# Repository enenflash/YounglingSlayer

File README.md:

# YounglingSlayer
Team repository for Robocup Junior Lightweight Australia 2024

## Team Info
- Members: Isabelle Tang (Captain), Ryan Beikrasouli (Programmer), Cruz Barry-Hardy (3D Designer), Albie Gardiner (3D Designer)
- State: Western Australia
- School: Rossmoyne Senior High School

## Programming
We use C++ in [ArduinoIDE](https://www.arduino.cc/en/software/) to program our microcontroller (Teensy 4.1). (See code-explanations)
We also use Raspberry Pi Pico as part of our line sensor.

## 3D Printing
We design our parts in [Fusion360](https://www.autodesk.com/au/products/fusion-360/education). (See mechanical design/)
All parts are printed in PLA.

## PCB Design
We design our PCBs in [KiCAD 7.0](https://www.kicad.org/) and order from [JLCPCB](https://jlcpcb.com/). (See pcbs/).
The schematics are based on circuits we tested using breadboards.

All designs are original other than the [BBR IR Seeker](https://irseeker.buildingblockrobotics.com/)

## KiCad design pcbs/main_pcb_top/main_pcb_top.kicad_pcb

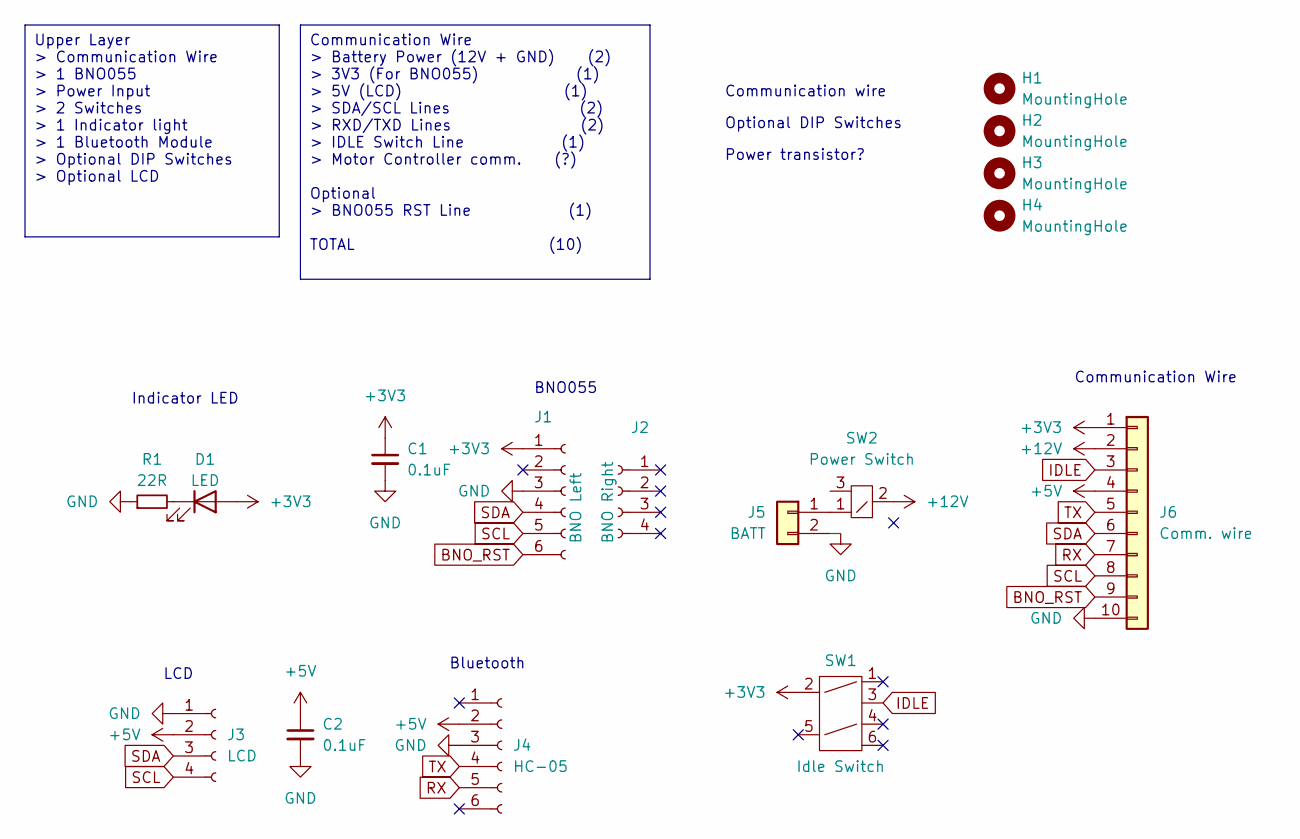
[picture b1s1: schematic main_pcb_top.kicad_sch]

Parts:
C1, C2: 0.1uF; C_0402_1005Metric
D1: LED; LED_0805_2012Metric
H1, H2, H3, H4: MountingHole; MountingHole_3.2mm_M3_Pad
J1: BNO Left; PinSocket_1x06_P2.54mm_Vertical
J2: BNO Right; PinSocket_1x04_P2.54mm_Vertical
J3: LCD; PinSocket_1x04_P2.54mm_Vertical
J4: HC-05; PinSocket_1x06_P2.54mm_Vertical
J5: BATT; JST_XH_B2B-XH-A_1x02_P2.50mm_Vertical
J6: Comm. wire; IDC-Header_2x05_P2.54mm_Vertical
R1: 22R; R_0805_2012Metric
SW1: Idle Switch; Switch_DPDT_S2060
SW2: Power Switch; Switch_SPDT_S2070

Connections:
+3V3: C1.1, D1.2 (A), J1.1, J6.1, SW1.2
+5V: C2.1, J3.2, J4.2, J6.4
+12V: J6.2, SW2.2
BNO_RST: J1.6, J6.9
GND: C1.2, C2.2, J1.3, J3.1, J4.3, J5.2, J6.10, R1.1
IDLE: J6.3, SW1.3
unnamed: D1.1 (K), R1.2
unnamed: J5.1, SW2.1
RX: J4.5, J6.7
SCL: J1.5, J3.4, J6.8
SDA: J1.4, J3.3, J6.6
TX: J4.4, J6.5

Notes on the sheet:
Upper Layer > Communication Wire > 1 BNO055 > Power Input > 2 Switches > 1 Indicator light > 1 Bluetooth Module > Optional DIP Switches > Optional LCD
Communication Wire > Battery Power (12V + GND) (2) > 3V3 (For BNO055) (1) > 5V (LCD) (1) > SDA/SCL Lines (2) > RXD/TXD Lines (2) > IDLE Switch Line (1) > Motor Controller comm. (?) Optional > BNO055 RST Line (1) TOTAL (10)
Power transistor?
Bluetooth
Communication wire
Optional DIP Switches
BNO055
LCD
Indicator LED
Communication Wire

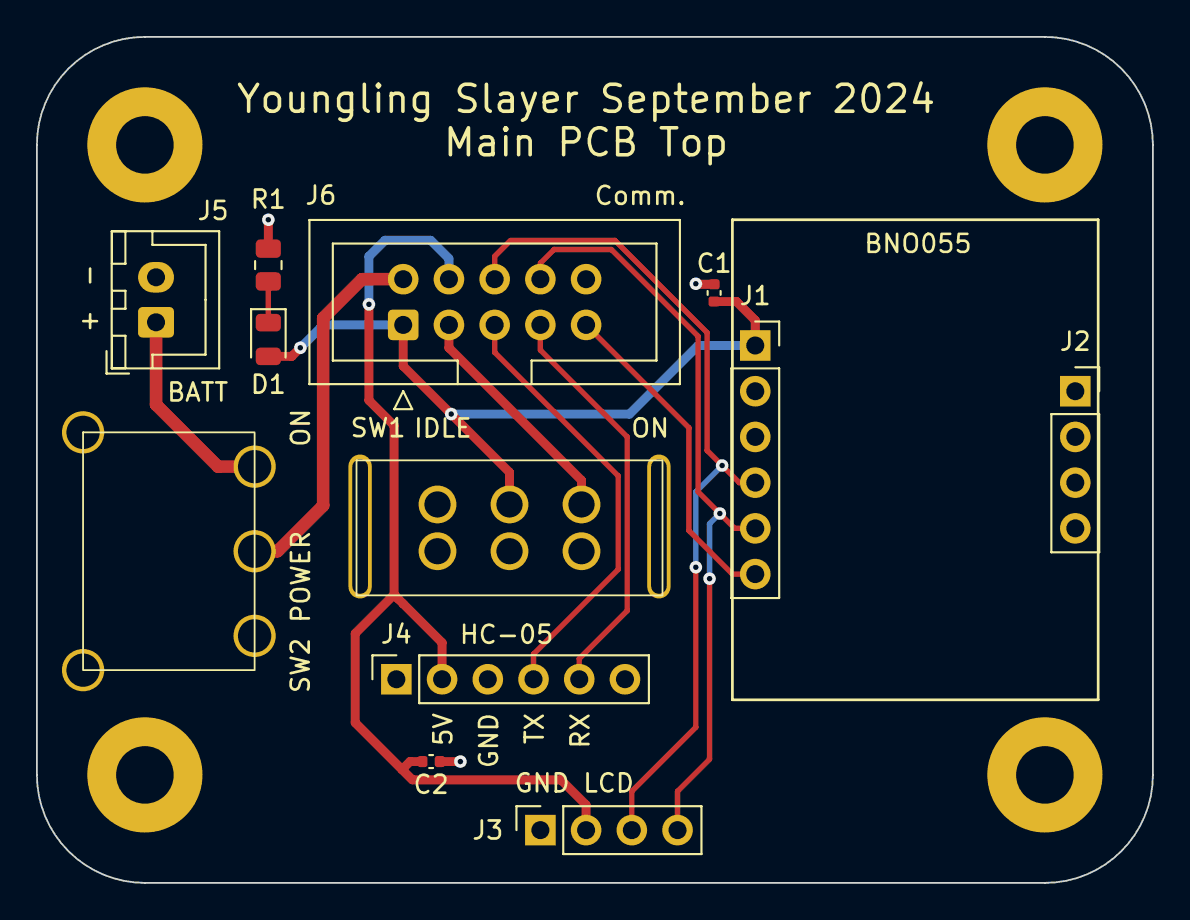
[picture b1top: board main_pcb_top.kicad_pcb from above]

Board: 2 copper layers, 62.0 x 47.0 mm, 16 parts (0 on the bottom side), 12 nets.

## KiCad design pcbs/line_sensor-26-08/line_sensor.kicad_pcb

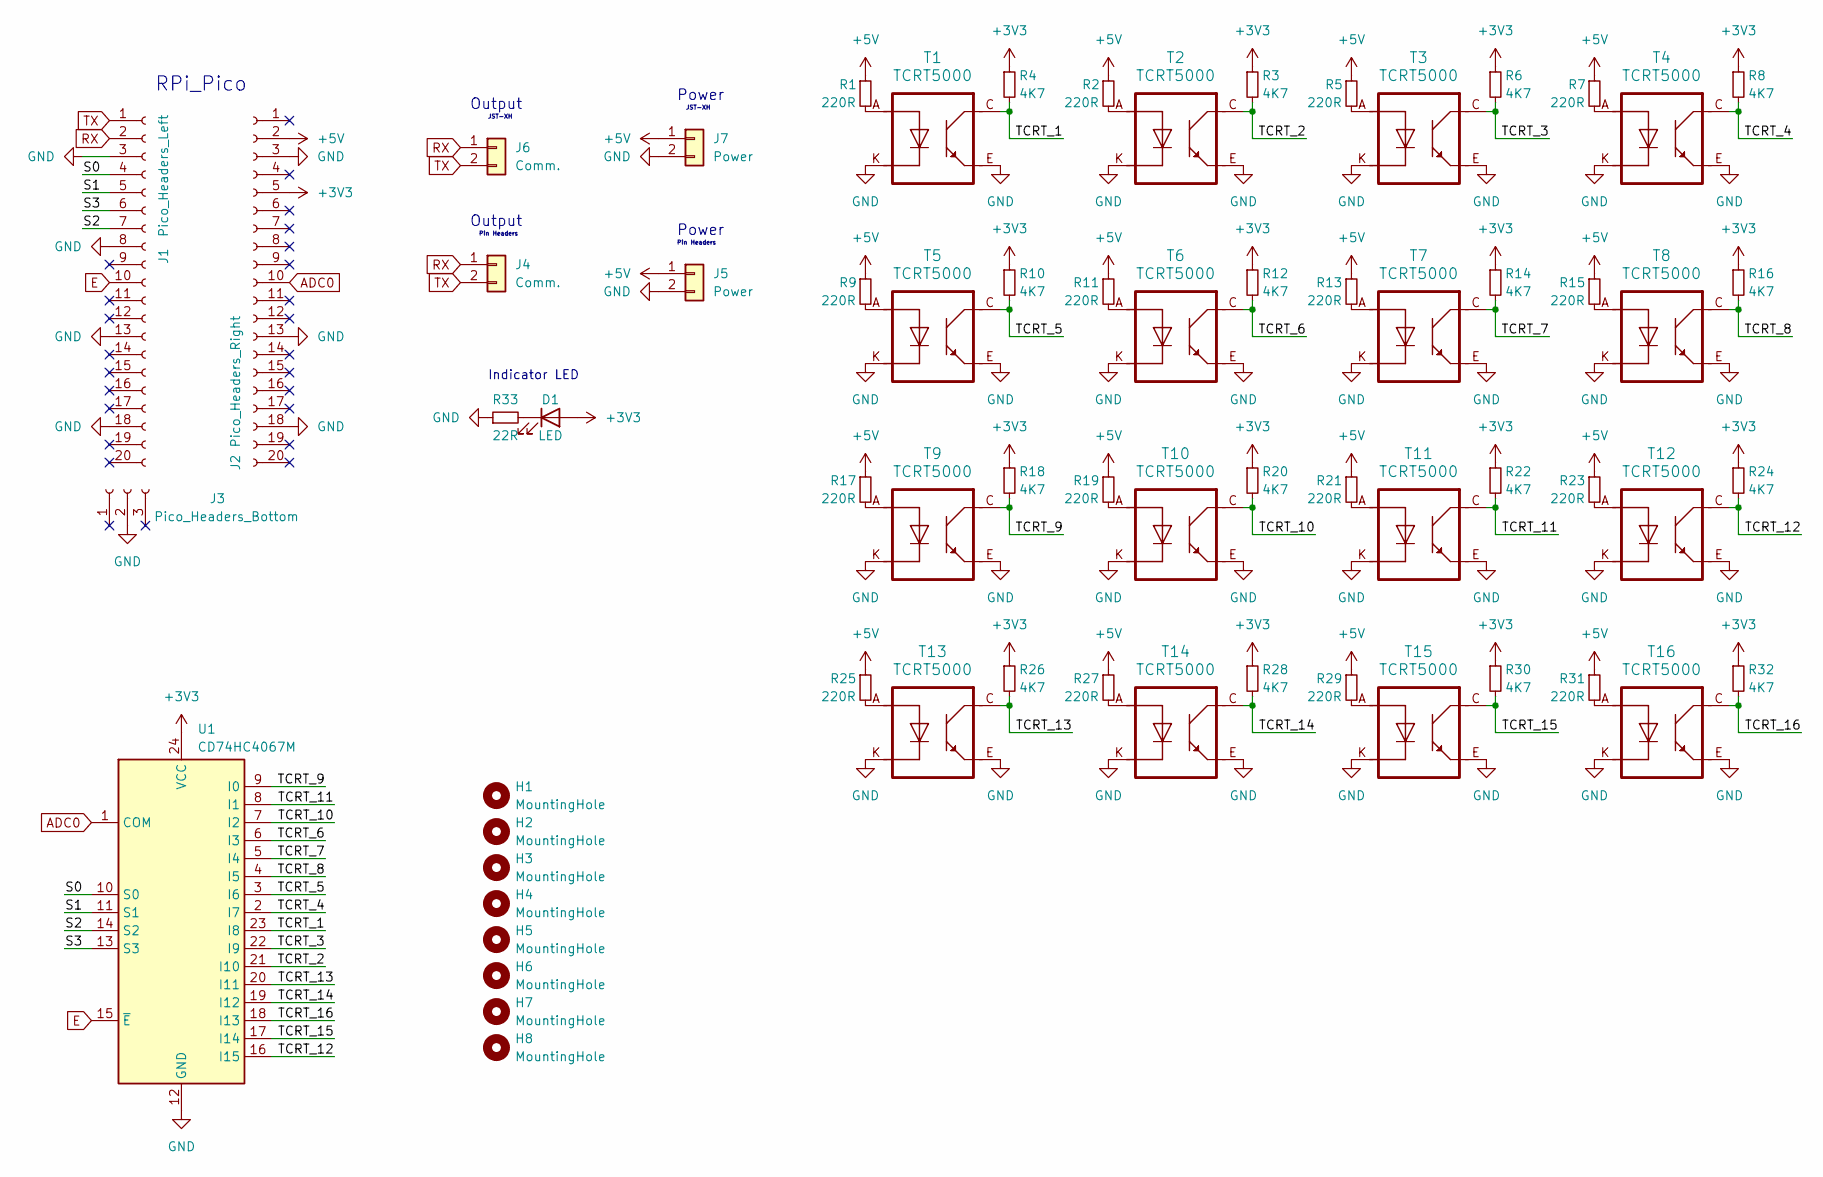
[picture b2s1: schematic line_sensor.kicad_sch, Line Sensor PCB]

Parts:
D1: LED; LED_0805_2012Metric
H1, H2, H3, H4, H5, H6, H7, H8: MountingHole; MountingHole_3.2mm_M3_Pad
J1: Pico_Headers_Left; PinSocket_1x20_P2.54mm_Vertical
J2: Pico_Headers_Right; PinSocket_1x20_P2.54mm_Vertical
J3: Pico_Headers_Bottom; PinSocket_1x03_P2.54mm_Vertical
J4: Comm.; PinSocket_1x02_P2.54mm_Vertical
J5: Power; PinSocket_1x02_P2.54mm_Vertical
J6: Comm.; JST_XH_B2B-XH-AM_1x02_P2.50mm_Vertical
J7: Power; JST_XH_B2B-XH-AM_1x02_P2.50mm_Vertical
R1, R2, R5, R7, R9, R11, R13, R15, R17, R19, R21, R23, R25, R27, R29, R31: 220R; R_0805_2012Metric
R3, R4, R6, R8, R10, R12, R14, R16, R18, R20, R22, R24, R26, R28, R30, R32: 4K7; R_0805_2012Metric
R33: 22R; R_0805_2012Metric
T1, T2, T3, T4, T5, T6, T7, T8, T9, T10, T11, T12, T13, T14, T15, T16: TCRT5000
U1: CD74HC4067M; SOIC-24W_7.5x15.4mm_P1.27mm

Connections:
+3V3: D1.2 (A), J2.5, R3.1, R4.1, R6.1, R8.1, R10.1, R12.1, R14.1, R16.1, R18.1, R20.1, R22.1, R24.1, R26.1, R28.1, R30.1, R32.1, U1.24 (VCC)
+5V: J2.2, J5.1, J7.1, R1.1, R2.1, R5.1, R7.1, R9.1, R11.1, R13.1, R15.1, R17.1, R19.1, R21.1, R23.1, R25.1, R27.1, R29.1, R31.1
/S0: J1.4, U1.10 (S0)
/S1: J1.5, U1.11 (S1)
/S2: J1.7, U1.14 (S2)
/S3: J1.6, U1.13 (S3)
/TCRT_1: R4.2, T1.C (Collector), U1.23 (I8)
/TCRT_2: R3.2, T2.C (Collector), U1.21 (I10)
/TCRT_3: R6.2, T3.C (Collector), U1.22 (I9)
/TCRT_4: R8.2, T4.C (Collector), U1.2 (I7)
/TCRT_5: R10.2, T5.C (Collector), U1.3 (I6)
/TCRT_6: R12.2, T6.C (Collector), U1.6 (I3)
/TCRT_7: R14.2, T7.C (Collector), U1.5 (I4)
/TCRT_8: R16.2, T8.C (Collector), U1.4 (I5)
/TCRT_9: R18.2, T9.C (Collector), U1.9 (I0)
/TCRT_10: R20.2, T10.C (Collector), U1.7 (I2)
/TCRT_11: R22.2, T11.C (Collector), U1.8 (I1)
/TCRT_12: R24.2, T12.C (Collector), U1.16 (I15)
/TCRT_13: R26.2, T13.C (Collector), U1.20 (I11)
/TCRT_14: R28.2, T14.C (Collector), U1.19 (I12)
/TCRT_15: R30.2, T15.C (Collector), U1.17 (I14)
/TCRT_16: R32.2, T16.C (Collector), U1.18 (I13)
ADC0: J2.10, U1.1 (COM)
E: J1.10, U1.15 (~E)
GND: J1.3, J1.8, J1.13, J1.18, J2.3, J2.13, J2.18, J3.2, J5.2, J7.2, R33.1, T1.E (Emitter), T1.K (Cathode), T2.E (Emitter), T2.K (Cathode), T3.E (Emitter), T3.K (Cathode), T4.E (Emitter), T4.K (Cathode), T5.E (Emitter), T5.K (Cathode), T6.E (Emitter), T6.K (Cathode), T7.E (Emitter), T7.K (Cathode), T8.E (Emitter), T8.K (Cathode), T9.E (Emitter), T9.K (Cathode), T10.E (Emitter), T10.K (Cathode), T11.E (Emitter), T11.K (Cathode), T12.E (Emitter), T12.K (Cathode), T13.E (Emitter), T13.K (Cathode), T14.E (Emitter), T14.K (Cathode), T15.E (Emitter), T15.K (Cathode), T16.E (Emitter), T16.K (Cathode), U1.12 (GND)
unnamed: D1.1 (K), R33.2
unnamed: R1.2, T1.A (Anode)
unnamed: R2.2, T2.A (Anode)
unnamed: R5.2, T3.A (Anode)
unnamed: R7.2, T4.A (Anode)
unnamed: R9.2, T5.A (Anode)
unnamed: R11.2, T6.A (Anode)
unnamed: R13.2, T7.A (Anode)
unnamed: R15.2, T8.A (Anode)
unnamed: R17.2, T9.A (Anode)
unnamed: R19.2, T10.A (Anode)
unnamed: R21.2, T11.A (Anode)
unnamed: R23.2, T12.A (Anode)
unnamed: R25.2, T13.A (Anode)
unnamed: R27.2, T14.A (Anode)
unnamed: R29.2, T15.A (Anode)
unnamed: R31.2, T16.A (Anode)
RX: J1.2, J4.1, J6.1
TX: J1.1, J4.2, J6.2

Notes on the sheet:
Output
Power
RPi_Pico
JST-XH
Pin Headers
Indicator LED

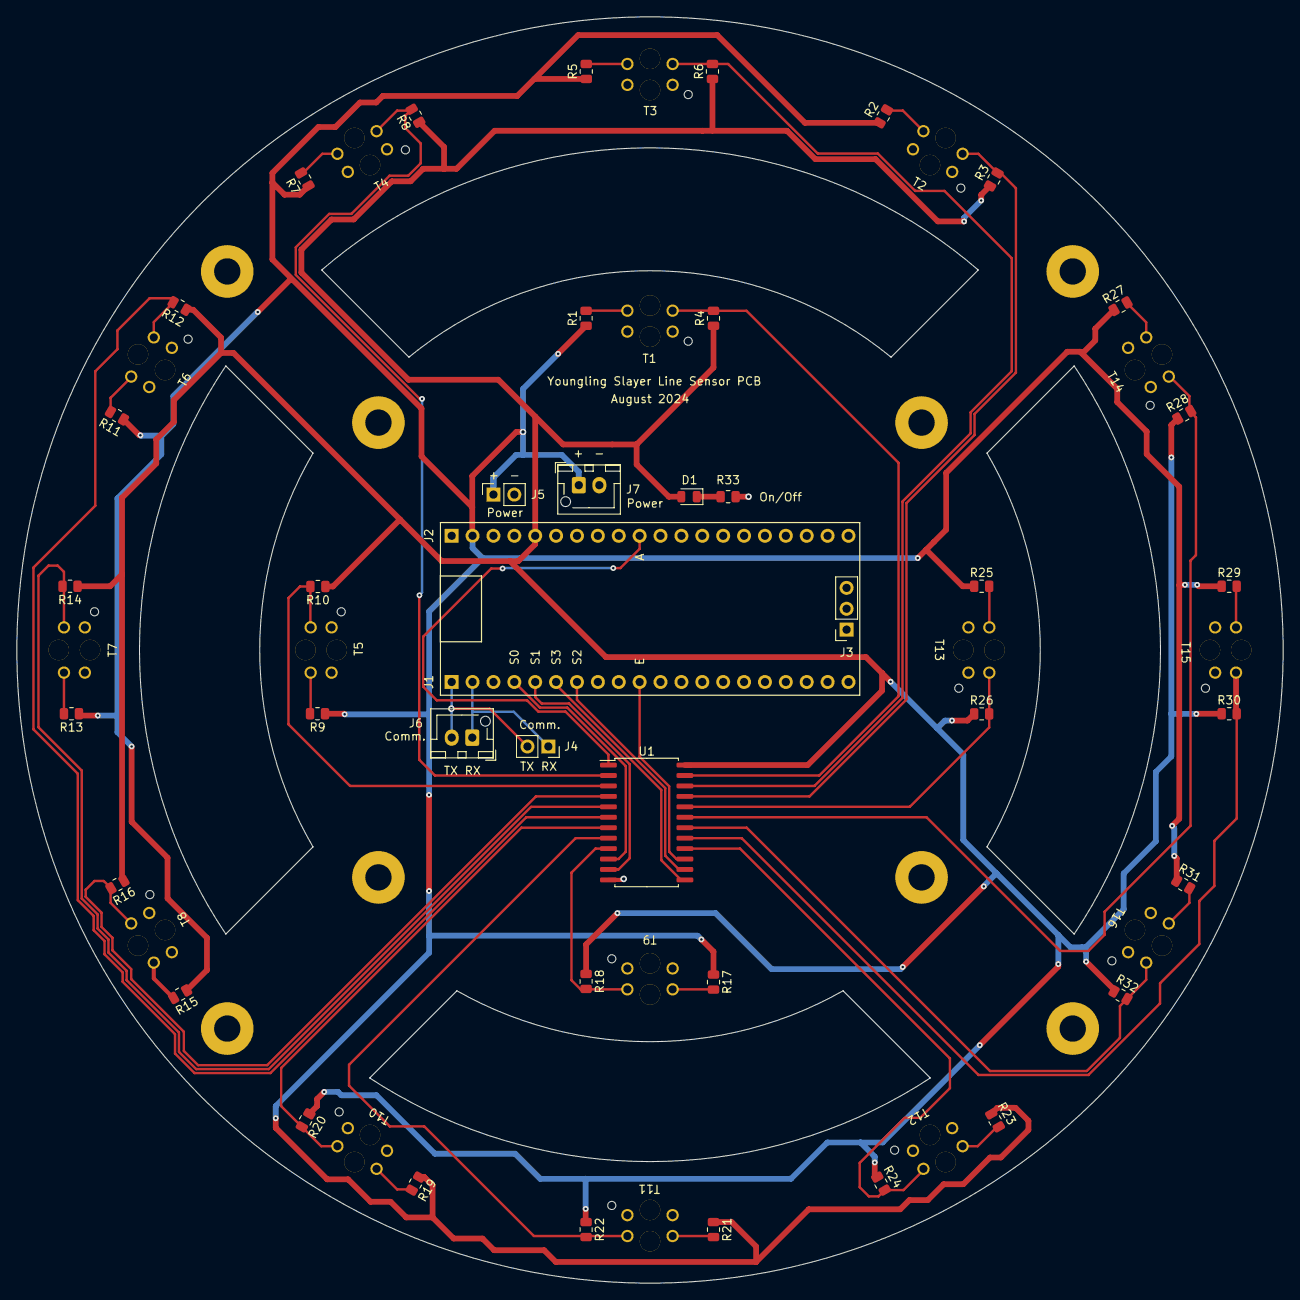
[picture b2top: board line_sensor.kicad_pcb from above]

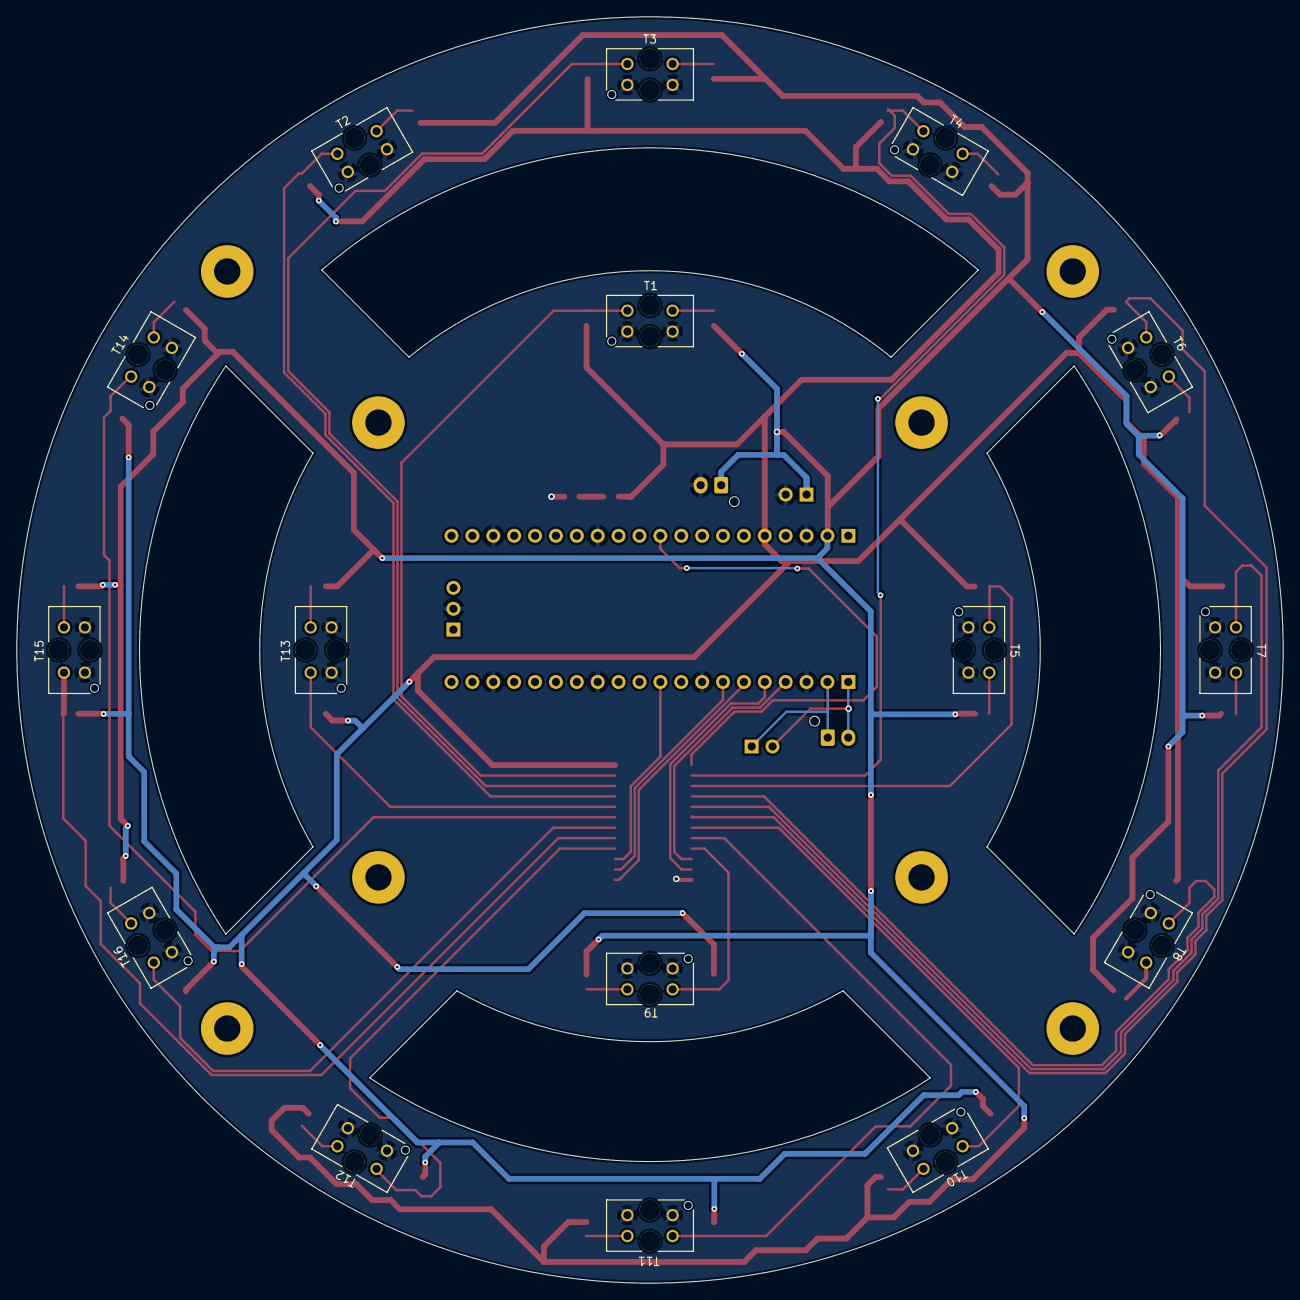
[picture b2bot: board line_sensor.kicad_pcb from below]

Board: 2 copper layers, 154.0 x 154.0 mm, 66 parts (16 on the bottom side), 44 nets.

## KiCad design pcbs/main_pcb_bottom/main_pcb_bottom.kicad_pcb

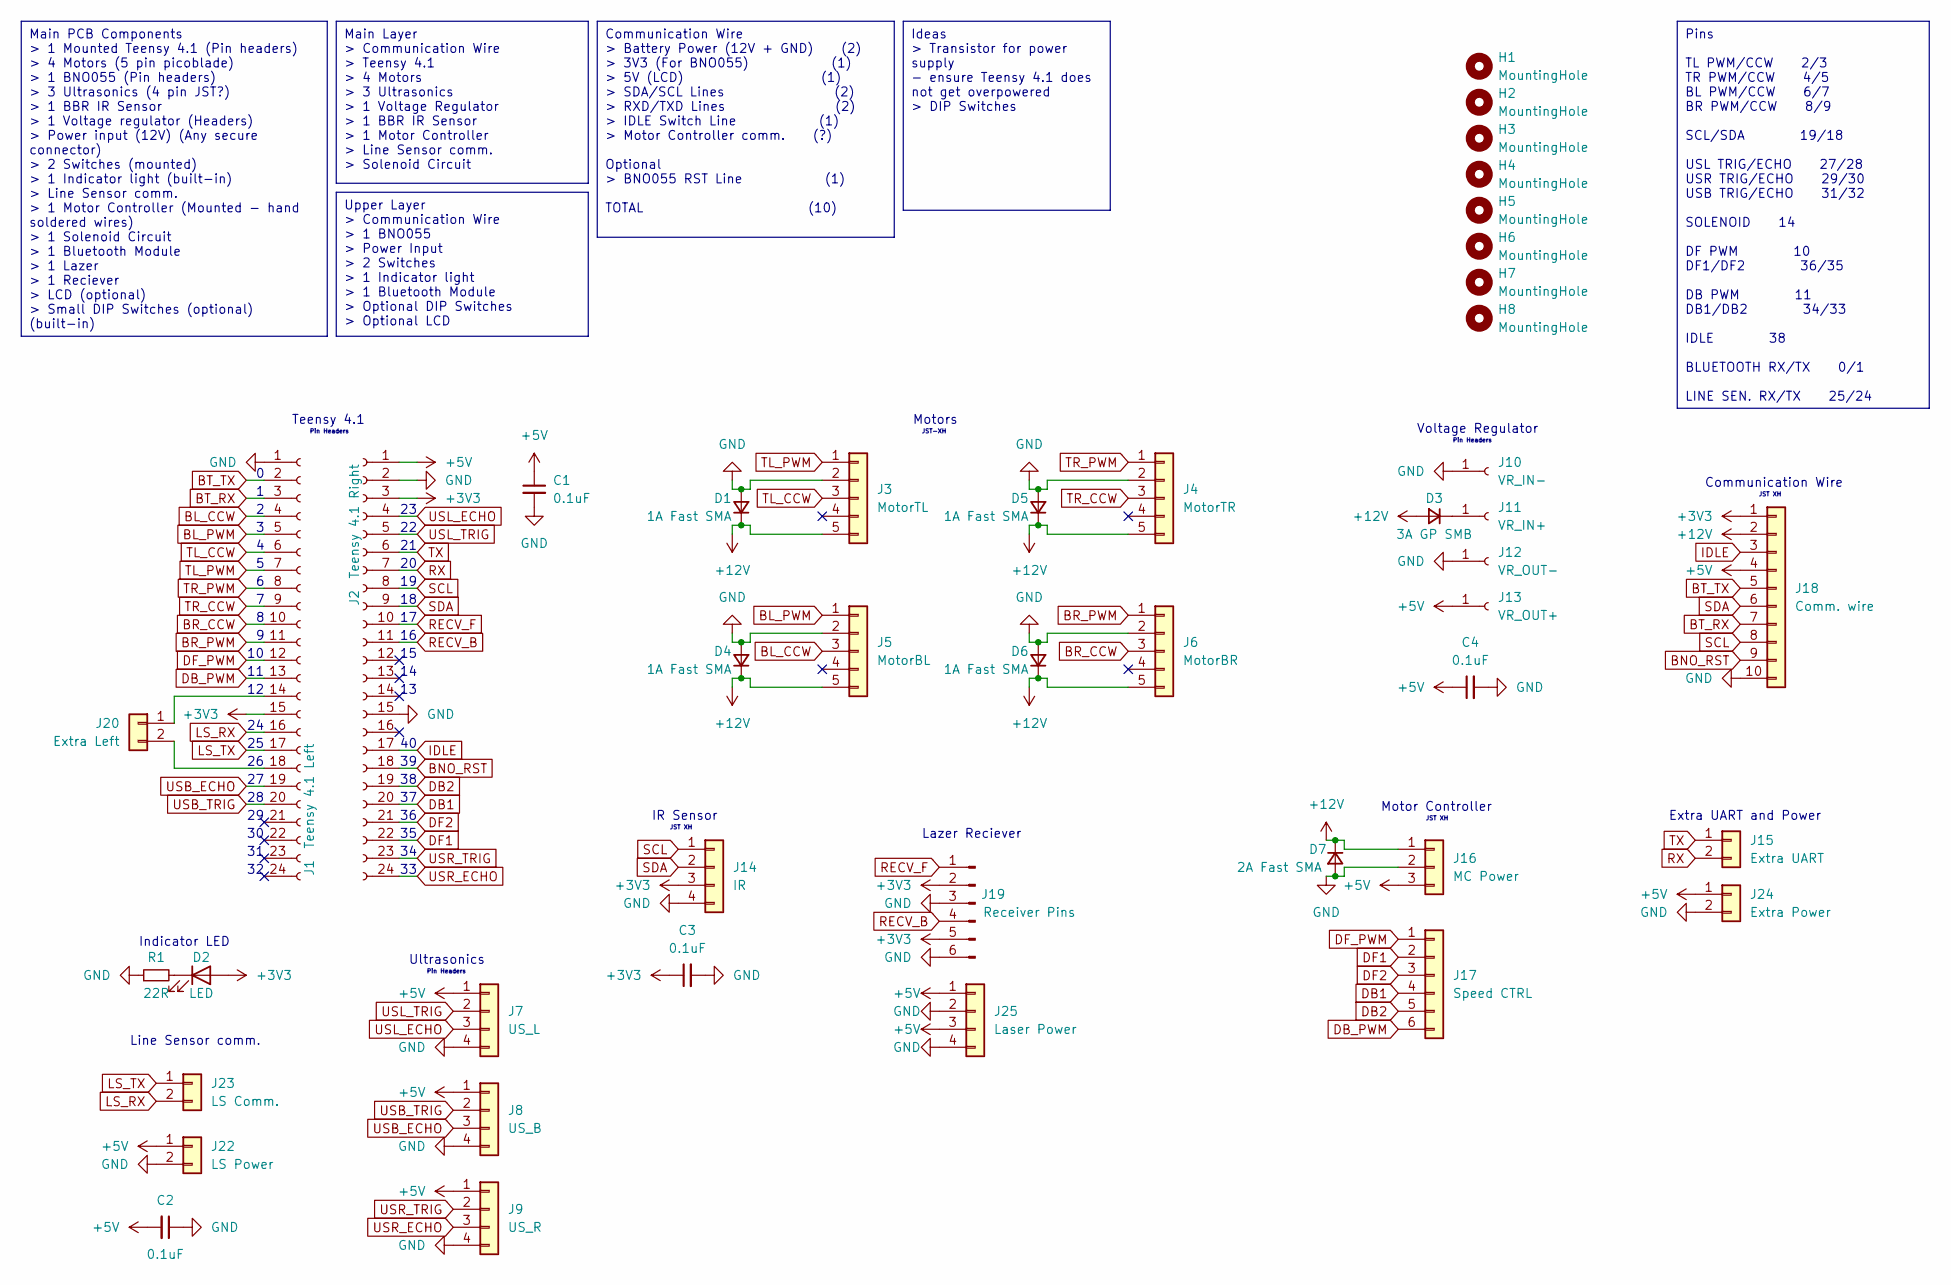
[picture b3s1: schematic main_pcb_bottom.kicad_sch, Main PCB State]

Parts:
C1, C2, C3, C4: 0.1uF; C_0402_1005Metric
D1, D4, D5, D6: 1A Fast SMA; D_SMA
D2: LED; LED_0805_2012Metric_Pad1.15x1.40mm_HandSolder
D3: 3A GP SMB; D_SMB
D7: 2A Fast SMA; D_SMA
H1, H2, H3, H4, H5, H6, H7, H8: MountingHole; MountingHole_3.2mm_M3_Pad
J1: Teensy 4.1 Left; PinSocket_1x24_P2.54mm_Vertical
J2: Teensy 4.1 Right; PinSocket_1x24_P2.54mm_Vertical
J3: MotorTL; JST_XH_B5B-XH-AM_1x05_P2.50mm_Vertical
J4: MotorTR; JST_XH_B5B-XH-AM_1x05_P2.50mm_Vertical
J5: MotorBL; JST_XH_B5B-XH-AM_1x05_P2.50mm_Vertical
J6: MotorBR; JST_XH_B5B-XH-AM_1x05_P2.50mm_Vertical
J7: US_L; JST_XH_B4B-XH-AM_1x04_P2.50mm_Vertical
J8: US_B; JST_XH_B4B-XH-AM_1x04_P2.50mm_Vertical
J9: US_R; JST_XH_B4B-XH-AM_1x04_P2.50mm_Vertical
J10: VR_IN-; PinSocket_1x01_P2.54mm_Vertical
J11: VR_IN+; PinSocket_1x01_P2.54mm_Vertical
J12: VR_OUT-; PinSocket_1x01_P2.54mm_Vertical
J13: VR_OUT+; PinSocket_1x01_P2.54mm_Vertical
J14: IR; JST_XH_B4B-XH-AM_1x04_P2.50mm_Vertical
J15: Extra UART; JST_XH_B2B-XH-AM_1x02_P2.50mm_Vertical
J16: MC Power; JST_XH_B3B-XH-AM_1x03_P2.50mm_Vertical
J17: Speed CTRL; JST_XH_B6B-XH-AM_1x06_P2.50mm_Vertical
J18: Comm. wire; IDC-Header_2x05_P2.54mm_Vertical
J19: Receiver Pins; PinHeader_1x06_P2.54mm_Vertical
J20: Extra Left; PinSocket_1x02_P2.54mm_Vertical
J22: LS Power; JST_XH_B2B-XH-AM_1x02_P2.50mm_Vertical
J23: LS Comm.; JST_XH_B2B-XH-AM_1x02_P2.50mm_Vertical
J24: Extra Power; JST_XH_B2B-XH-AM_1x02_P2.50mm_Vertical
J25: Laser Power; PinHeader_1x04_P2.54mm_Vertical
R1: 22R; R_0805_2012Metric_Pad1.20x1.40mm_HandSolder

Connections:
+3V3: C3.1, D2.2 (A), J1.15, J2.3, J14.3, J18.1, J19.2, J19.5
+5V: C1.1, C2.2, C4.1, J2.1, J7.1, J8.1, J9.1, J13.1, J16.3, J18.4, J22.1, J24.1, J25.1, J25.3
+12V: D1.1 (K), D3.2 (A), D4.1 (K), D5.1 (K), D6.1 (K), D7.1 (K), J3.5, J4.5, J5.5, J6.5, J16.1, J18.2
BL_CCW: J1.4, J5.3
BL_PWM: J1.5, J5.1
BNO_RST: J2.18, J18.9
BR_CCW: J1.10, J6.3
BR_PWM: J1.11, J6.1
BT_RX: J1.3, J18.7
BT_TX: J1.2, J18.5
DB1: J2.20, J17.4
DB2: J2.19, J17.5
DB_PWM: J1.13, J17.6
DF1: J2.22, J17.2
DF2: J2.21, J17.3
DF_PWM: J1.12, J17.1
GND: C1.2, C2.1, C3.2, C4.2, D1.2 (A), D4.2 (A), D5.2 (A), D6.2 (A), D7.2 (A), J1.1, J2.2, J2.15, J3.2, J4.2, J5.2, J6.2, J7.4, J8.4, J9.4, J10.1, J12.1, J14.4, J16.2, J18.10, J19.3, J19.6, J22.2, J24.2, J25.2, J25.4, R1.1
IDLE: J2.17, J18.3
LS_RX: J1.16, J23.2
LS_TX: J1.17, J23.1
unnamed: D2.1 (K), R1.2
unnamed: D3.1 (K), J11.1
unnamed: J1.14, J20.1
unnamed: J1.18, J20.2
RECV_B: J2.11, J19.4
RECV_F: J2.10, J19.1
RX: J2.7, J15.2
SCL: J2.8, J14.1, J18.8
SDA: J2.9, J14.2, J18.6
TL_CCW: J1.6, J3.3
TL_PWM: J1.7, J3.1
TR_CCW: J1.9, J4.3
TR_PWM: J1.8, J4.1
TX: J2.6, J15.1
USB_ECHO: J1.19, J8.3
USB_TRIG: J1.20, J8.2
USL_ECHO: J2.4, J7.3
USL_TRIG: J2.5, J7.2
USR_ECHO: J2.24, J9.3
USR_TRIG: J2.23, J9.2

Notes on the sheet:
Upper Layer > Communication Wire > 1 BNO055 > Power Input > 2 Switches > 1 Indicator light > 1 Bluetooth Module > Optional DIP Switches > Optional LCD
Main Layer > Communication Wire > Teensy 4.1 > 4 Motors > 3 Ultrasonics > 1 Voltage Regulator > 1 BBR IR Sensor > 1 Motor Controller > Line Sensor comm. > Solenoid Circuit
Main PCB Components > 1 Mounted Teensy 4.1 (Pin headers) > 4 Motors (5 pin picoblade) > 1 BNO055 (Pin headers) > 3 Ultrasonics (4 pin JST?) > 1 BBR IR Sensor > 1 Voltage regulator (Headers) > Power input (12V) (Any secure connector) > 2 Switches (mounted) > 1 Indicator light (built-in) > Line Senso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
Pins TL PWM/CCW 2/3 TR PWM/CCW 4/5 BL PWM/CCW 6/7 BR PWM/CCW 8/9 SCL/SDA 19/18 USL TRIG/ECHO 27/28 USR TRIG/ECHO 29/30 USB TRIG/ECHO 31/32 SOLENOID 14 DF PWM 10 DF1/DF2 36/35 DB PWM 11 DB1/DB2 34/33 IDLE 38 BLUETOOTH RX/TX 0/1 LINE SEN. RX/TX 25/24
Ideas > Transistor for power supply - ensure Teensy 4.1 does not get overpowered > DIP Switches
Communication Wire > Battery Power (12V + GND) (2) > 3V3 (For BNO055) (1) > 5V (LCD) (1) > SDA/SCL Lines (2) > RXD/TXD Lines (2) > IDLE Switch Line (1) > Motor Controller comm. (?) Optional > BNO055 RST Line (1) TOTAL (10)
Motors
JST-XH
Teensy 4.1
Communication Wire
Lazer Reciever
JST XH
Pin Headers
Line Sensor comm.
Voltage Regulator
Indicator LED
IR Sensor
Motor Controller
Extra UART and Power
Ultrasonics

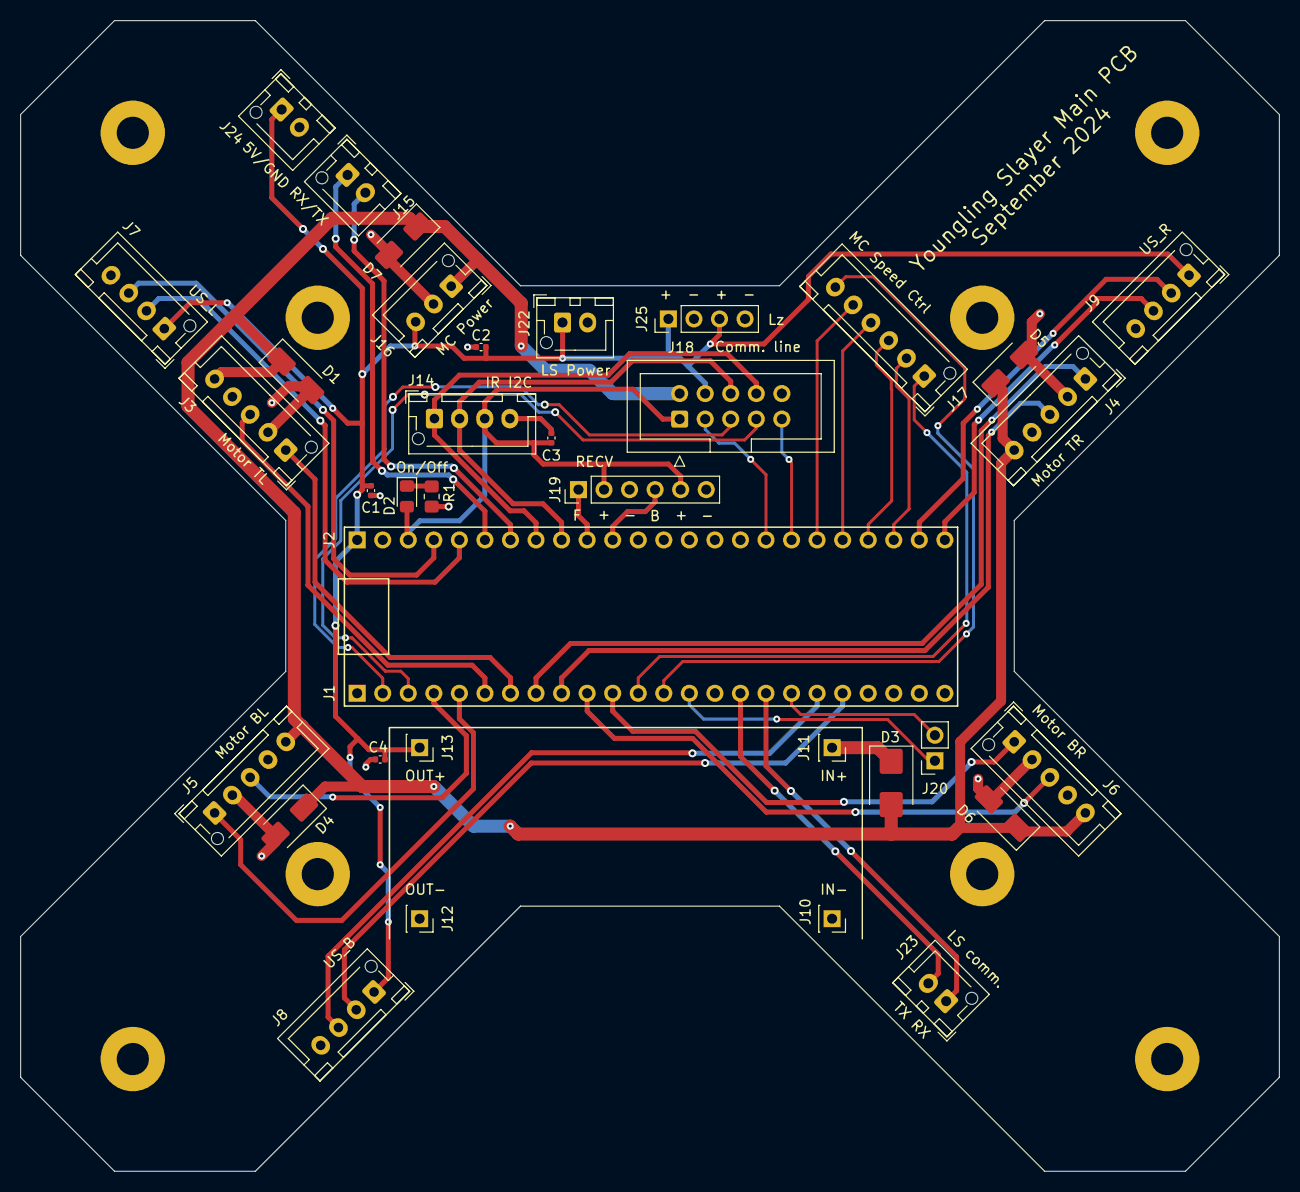
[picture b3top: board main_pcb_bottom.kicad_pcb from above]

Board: 2 copper layers, 125.1 x 114.4 mm, 44 parts (0 on the bottom side), 40 nets.

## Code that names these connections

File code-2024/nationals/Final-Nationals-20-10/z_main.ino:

Robot bot;
bool idle = true;

/* :::::::: SETUP :::::::: */
void setup() {
  Serial.begin(9600);
  Serial.println("\nRobot Initialized");

  Serial6.begin(9600);

  pinMode(IDLE_PIN, INPUT);

  /* :::::::: MOTOR PINS :::::::: */
  pinMode(TL_PWM, OUTPUT);
  pinMode(TR_PWM, OUTPUT);
  pinMode(BL_PWM, OUTPUT);
  pinMode(BR_PWM, OUTPUT);

  analogWriteFrequency(TL_PWM, 20000);
  analogWriteFrequency(TR_PWM, 20000);
  analogWriteFrequency(BL_PWM, 20000);
  analogWriteFrequency(BR_PWM, 20000);

  pinMode(TL_DIR, OUTPUT);
  pinMode(TR_DIR, OUTPUT);
  pinMode(BL_DIR, OUTPUT);
  pinMode(BR_DIR, OUTPUT);

  /* :::::::: ULTR PINS :::::::: */

  pinMode(USL_TRIG, OUTPUT);
  pinMode(USR_TRIG, OUTPUT);
  pinMode(USB_TRIG, OUTPUT);
  pinMode(USL_ECHO, INPUT);
  pinMode(USR_ECHO, INPUT);
  pinMode(USB_ECHO, INPUT);

  pinMode(IDLE_PIN, INPUT_PULLDOWN);

  bot.mc.stopMotors();
  
  // IMU
  if (!bot.bno.begin()) { Serial.print("\nNo BNO055 detected"); }
  else { Serial.println("\nBNO055 Initialized"); }
  bot.bno.setExtCrystalUse(true);

  // IR
  Wire.begin();
}

/* :::::::: DEBUGGING :::::::: */

void printIR() {
  Serial.print("Direction: ");
  Serial.print(bot.direction);
  Serial.print(" Strength: ");
  Serial.println(bot.strength);
};

void printMovement() {
  Serial.print("MoveX: ");
  Serial.print(bot.x);
  Serial.print(" MoveY: ");
  Serial.print(bot.y);
  Serial.print(" Speed: ");
  Serial.println(bot.mc.getSpeed());
};

void printLine() {
  Serial.print("Line: ");
  Serial.println(bot.lineValue);
};

/* :::::::: MAIN :::::::: */
void loop() {
  // check idle switch
  if (idle) {
    if (digitalRead(IDLE_PIN) == HIGH) {
      idle = false;
    }
    else {  
      return;
    }
  }

  bot.update();
  // bot.direction = 12;
  // bot.x = 0, bot.y = 0;
  if (bot.direction == 12) {
    bot.targetGoal();
    bot.getOffset();
  }
  else {
    bot.getBehindBall();
  }

  if (bot.direction != 12 && bot.direction != 11 && bot.direction != 1) {
    bot.offset = 0;
  }

  bot.stopAtLine();

  Serial.print("Direction: ");
  Serial.print(bot.direction);
  Serial.print(" Strength: ");
  Serial.println(bot.strength);

  bot.ps.serialPrint();
  
  printLine();

  bot.adjustSpeed();
  bot.logY();
  bot.run();
}

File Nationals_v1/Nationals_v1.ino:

#include <iostream>
#include <array> // to import imutable arrays with set size
#include <cmath> // for trig
#include <algorithm> 
#include <map> // dictionaries
#include <vector> // mutable lists with no set size
#include <numeric> // used for calculating sum of vectors
#include <SoftwareSerial.h> // bluetooth
SoftwareSerial bluetooth(0, 1); // pin 0 and 1 Rx and Tx


// For IMU
#include <Wire.h>
#include <Adafruit_Sensor.h>
#include <Adafruit_BNO055.h>
#include <utility/imumaths.h>

using namespace std;

// motor pins    // pins on PCB
#define BL_PWM 7 // 4
#define BL_DIR 8 // 3

#define TL_PWM 11 // 6
#define TL_DIR 12 // 5

#define TR_PWM 1 // 7 
#define TR_DIR 2 // 8 

#define BR_PWM 3 // 10
#define BR_DIR 4 // 9

// ultrasonic pins
#define LU_TRIG 35 // 22
#define LU_ECHO 34 // 23

#define RU_TRIG 41 // 34
#define RU_ECHO 40 // 33

#define BU_TRIG 21 // 28
#define BU_ECHO 20 // 27

// dribbler motors
#define DF_PWM 10
#define DF_DIR1 35
#define DF_DIR2 36
#define DB_PWM 11
#define DB_DIR1 37
#define DB_DIR2 38

// other pins
#define SWITCH_PIN 36 // 40
#define FLDR 17
#define BLDR 16

// other variables
#define MIN_BALL_DISTANCE 65 // any less than 65 and it counts as close
#define MAX_SPEED 100

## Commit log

2024-05-21 test_commit
2024-05-21 test_commit_2
2024-05-21 cruz_commit
2024-05-21 fix_commit
2024-05-21 test_2
2024-05-21 Ryan has entered 😎
2024-05-21 updated readme with team members
2024-05-21 added mechanical design folder
2024-05-21 added pcb folder
2024-05-21 Create stuff
2024-05-21 added gyro test program
2024-05-21 deleted unnecessary file
2024-05-21 fixed ryans spelling mistakes
2024-05-21 added links.txt
2024-05-21 deleted un
2024-05-26 Added testing codes
    Codes for testing:
    Laser
    ultrasonic
    motors
    gyro
2024-06-07 Added new test codes for LCD, IR and all motors
2024-06-15 <-- THIS IS UPDATED CODE
    - updated for loops
    - changed 'idle' to match test motor
2024-06-17 change int coords to float
2024-06-17 added comments
2024-06-17 added example code
2024-06-17 added 3mf files
2024-06-19 correct tangent errors for Q2, Q3 and Q4
2024-06-19 added outdated warning
2024-06-19 added round to motor ratio
2024-06-19 Create motor_controller.cpp
    this code is for pure c++
    follow the instructions at the top to run in arduinoIDE
2024-06-19 added >100 <-100 speed check
2024-06-20 Updated pins.txt
2024-07-02 fixed -0 issue
2024-08-19 Added code_V1
2024-08-19 Added code_V2
    this version is still to be updated and is unfinished
2024-08-19 Added teensy 4.1 - rasberry pi pico communication
    one file to be run on teensy (TeensyRP_Teensy.ino) and one to be run on the rasberrry pi pico (TeensyRP_RP.ino)
2024-08-19 Added updated roles, added Albie and newest code version
2024-08-20 Updated Code_V2
2024-08-24 updated code_V1
2024-08-24 Updated Code_V1 24 Aug 6:47pm(DOES NOT INCLUDE US)
2024-08-24 25th aug 12:27am Code_V1 update
    When running remove "copy" from file name
2024-08-25 Final Code_V1 used in state
    Congratulations on the win again guys. It was well deserved.
2024-09-14 Added dribbler testing and nationals_V1
    just uncomment the sections one by one in nationals_V1 to test. please do not burn teensys and do not let Cruz touch the code
2024-09-14 Added bluetooth testing
2024-09-15 Updated version and corrected errors
2024-09-19 Colour sensor testing code (directly with RP)
    Does not communicate with teensy prints readings directly from RP
2024-09-25 LS test code returns bool for white line
2024-09-27 created nationals folder with robot class test
2024-09-27 add files to robot class
2024-09-27 Rearranged files (no deletes)
2024-09-27 added pcbs.txt
2024-09-28 added pcbs
2024-09-28 updated link.txt
2024-09-28 added ir.cpp
    filters direction within class
2024-09-28 added robot.cpp
    use in ino file and include other classes
2024-09-28 created prototype_ls_code.ino
2024-10-02 added folder structure and some state designs
2024-10-02 added design notes to metro
2024-10-02 added files to metro
2024-10-05 added goal tilt and other features
2024-10-05 fixed ps.y issue
    y = FIELD_WIDTH - trueBack;
    FIELD_LENGTH not FIELD_WIDTH
2024-10-05 added FIELD_LENGTH
2024-10-06 added components list
2024-10-06 state designs
2024-10-06 nationals designs
2024-10-09 added code explanations
2024-10-13 fixed write(0) error
2024-10-14 update robot goal tilt
2024-10-14 anti own goal additions
2024-10-14 line sensor changes
2024-10-15 updated stay within the lines
2024-10-15 updated comments
2024-10-15 added bluetooth class and file
2024-10-15 fixed undefined team data
2024-10-16 updated stopAtLine
2024-10-17 Added go forward at start but commented out
2024-10-17 fixed speed calculation
2024-10-17 added delay
2024-10-17 fixed go forward at start
2024-10-17 added codes commented out until future
2024-10-17 comments
2024-10-17 fixed getSpeed function missing
2024-10-17 fixed
2024-10-17 Added going forwards at start
2024-10-17 Fixed moving around ball hesitation
2024-10-17 speed
2024-10-17 strength range
2024-10-17 send data
2024-10-17 updated update bluetooth
2024-10-17 teamStr var
2024-10-17 added defence check
2024-10-17 added defence check code
2024-10-17 bluetooth begin added
2024-10-17 manual defend goal
2024-10-18 code exp gone
2024-10-18 code rewrite
2024-10-18 update ultrasonics
2024-10-19 8:50 code
2024-10-19 10:55 fixed errors
2024-10-19 1:32 changes
2024-10-19 new ps class
2024-10-19 19_10 update
2024-10-19 dir 6 fixed
2024-10-19 updated nationals 19-10
2024-10-19 fixed front and back stay within lines
2024-10-19 commented
2024-10-20 added final nationals
